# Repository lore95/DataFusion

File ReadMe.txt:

Project: ML Video Recognition & Pressure Boards for Post-Surgery Knee Rehabilitation @ KTH

INTRODUCTION
This project integrates machine learning-based video recognition and pressure boards to combine extrapolated data, generating an accurate 3D model of forces and human body movement. The main goal is to evaluate a patient's muscular power and movement fluidity, essential for monitoring progress in post-surgery knee rehabilitation.

PROBLEM STATEMENT
Evaluating muscle power and movement fluidity is crucial for tracking post-surgery recovery in patients with knee injuries. Traditionally, physiotherapists rely on qualitative assessments or expensive equipment to obtain reliable data. This project aims to provide a cost-effective, accurate, and universal solution for precise measurements through force sensors and skeleton tracking technology.

SOLUTION
Our system leverages data from four force sensors on a Wii board combined with video-based skeleton tracking to offer enhanced evaluations of knee recovery. By providing precise metrics, it complements and improves traditional methods of physiotherapy, offering a more data-driven approach to post-surgery rehabilitation.

HOW IT WORKS
Force Sensors: Four force sensors from a Wii board collect data on pressure distribution during movement.
Skeleton Tracking: Video-based skeleton tracking technology captures the movement and alignment of the patient's body.
Data Integration: Both sources of data are combined to create a 3D model that visualizes forces and motion, allowing for detailed analysis of knee recovery progress.

CONTRIBUTING
We welcome contributions! Please feel free to submit a pull request or raise an issue to discuss improvements or report bugs.

PROJECT STRUCTURE
Src/DataFusionExe
-DataFusion.py
	This file contains the code responsible for merging the data from the two core technologies used in this project: force sensors from the Wii board and video-based skeleton tracking. The integration of these datasets allows for the creation of a detailed and accurate 3D model, which is essential for evaluating a patient's post-surgery knee recovery.

-ImageRecognition AND PressureReadings:
	The folder ImageRecognition contains all the code related to skeleton tracking development and testing.
	The folder PressureReadings contains the implementation for reading force data from the Wii board's sensors.

-Requirements.txt
	The requirements.txt file lists all necessary dependencies for the project.

-yolov8m-pose.pt
	We use the yolov8m-pose.pt model for skeleton tracking.

INSTALLATION (WIP)
Clone the repository: git clone https://github.com/lore95/DataFusion.git
Install dependencies: pip install -r requirements.txt
Follow the steps in the Readme file located in PressureReadings
Run the application: python DataFusion.py

USAGE
Connect the Wii board to your USB port.
Start collecting data for post-surgery knee rehabilitation analysis.

The project communication channel: https://app.clickup.com/9012214187/v/b/s/90121097948

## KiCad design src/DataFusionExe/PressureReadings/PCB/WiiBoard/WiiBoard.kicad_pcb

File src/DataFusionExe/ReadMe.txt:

DATA INTEGRATION: FORCE SENSORS AND SKELETON TRACKING
This section contains the code responsible for merging the data from the two core technologies used in this project: force sensors from the Wii board and video-based skeleton tracking. The integration of these datasets allows for the creation of a detailed and accurate 3D model, which is essential for evaluating a patient's post-surgery knee recovery.

- The folder ImageRecognition contains all the code related to skeleton tracking development.
- The folder PressureReadings contains the implementation for reading force data from the Wii board's sensors.
- The script DataFusion.py integrates the data from both sources and runs the program.
- The requirements.txt file lists all necessary dependencies for the project.
- We use the yolov8m-pose.pt model for skeleton tracking.

INSTALLATION (WIP)
Clone the repository: git clone https://github.com/lore95/DataFusion.git
Install dependencies: pip install -r requirements.txt
Run the application: python DataFusion.py

USAGE
Connect the Wii board to your USB port.
Launch the video recognition system.
Start collecting data for post-surgery knee rehabilitation analysis.

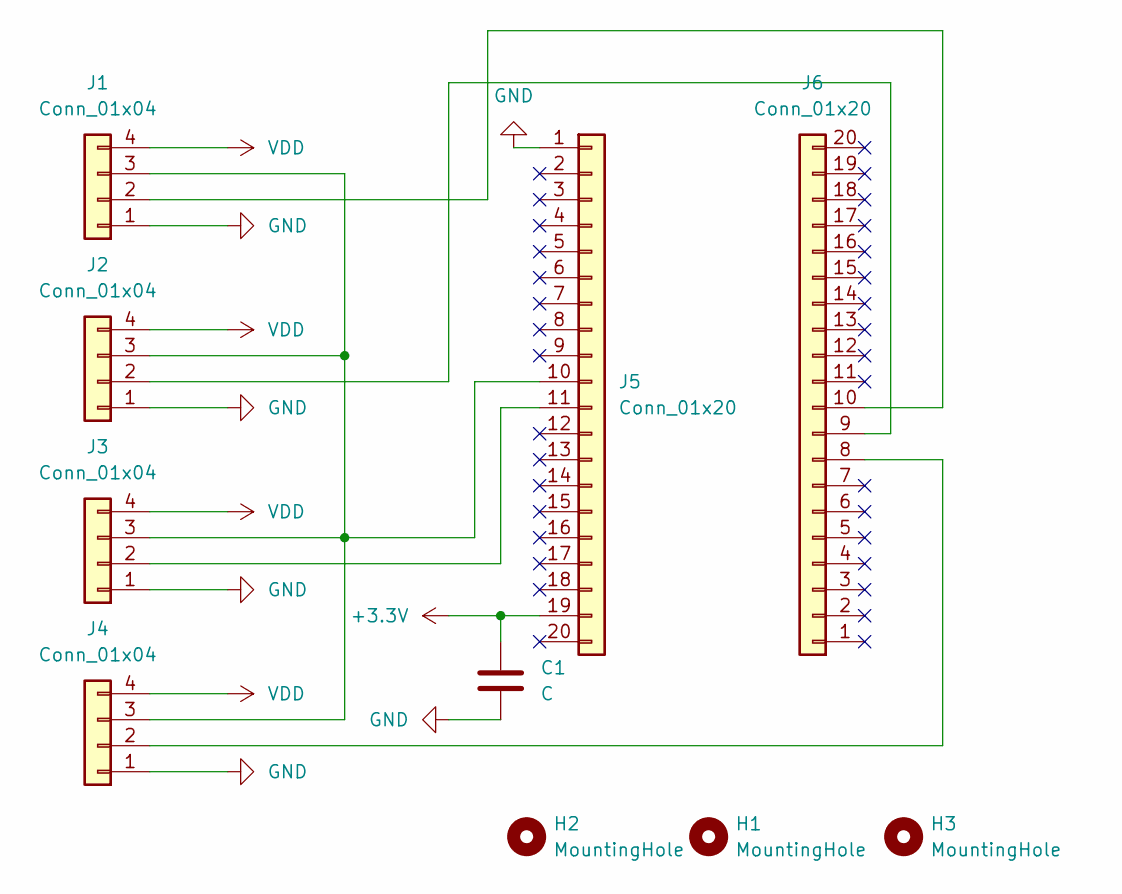
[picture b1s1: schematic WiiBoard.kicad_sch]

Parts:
C1: C; CP_Radial_D8.0mm_P5.00mm
H1, H2, H3: MountingHole; MountingHole_3.2mm_M3
J1, J2, J3, J4: Conn_01x04; PinSocket_1x04_P2.54mm_Vertical
J5, J6: Conn_01x20; PinSocket_1x20_P2.54mm_Vertical

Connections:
+3.3V: C1.1, J5.19
GND: C1.2, J1.1, J2.1, J3.1, J4.1, J5.1
unnamed: J1.2, J6.10
unnamed: J1.3, J2.3, J3.3, J4.3, J5.10
unnamed: J2.2, J6.9
unnamed: J3.2, J5.11
unnamed: J4.2, J6.8
VDD: J1.4, J2.4, J3.4, J4.4

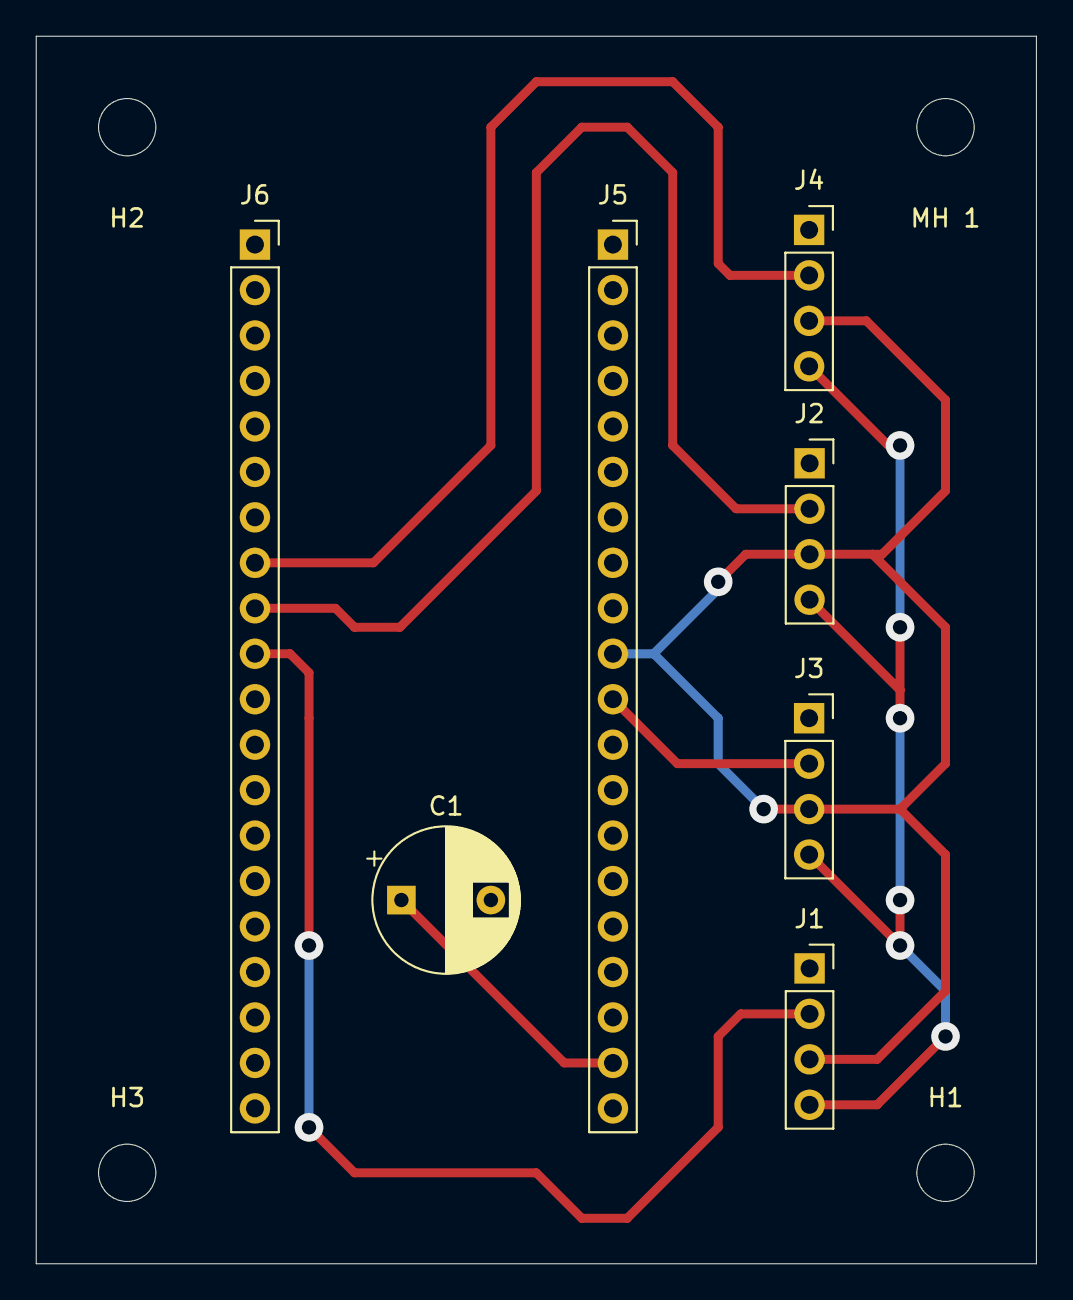
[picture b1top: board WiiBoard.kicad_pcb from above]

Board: 2 copper layers, 55.9 x 68.6 mm, 11 parts (0 on the bottom side), 8 nets.

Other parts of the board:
MH 1: MountingHole; MountingHole_3.2mm_M3

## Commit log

2024-08-29 GitHub Project Setup
2024-08-29 Update ReadMe.txt
    Just trying out
2024-08-29 Update ReadMe.txt
    Removed trash
2024-08-29 Changed clickuplink to go to board
2024-08-31 Added some files
2024-08-31 set up of structured folders for coding
2024-09-02 moves the lean canvas pdf to documentation folder
2024-09-02 Created instruction folder for openpose compilation on mac
2024-09-02 created a git ignore
2024-09-02 fixed gitignore
2024-09-19 Add files via upload
    Moved pdf to documentation folder
2024-09-19 Added ligament reconstruction pdf
2024-09-19 Renameve canvas and moved other pdf
2024-09-19 Fixed name for another pdf
2024-09-19 Ignore playground
2024-09-19 Fixed name of documentation folder
2024-09-23 wiiboard upload
2024-09-25 new wiiboard folder
2024-09-25 calibration data process
2024-09-27 experiment trials
    first equation good
2024-09-27 Experiment
    V1, V3 and V4 readings with gain 128
2024-09-27 for gain 1 and sps 40
2024-09-30 measurements with 640 SPS and 128 gain
2024-09-30 update sensitivity script
2024-09-30 V3_640_128 readings and png
2024-09-30 PLOT reg
2024-10-03 cleaning the folder pressur reading and creating a readme
2024-10-08 Fixed pathing and folder names, added skeleton tracking
2024-10-08 update location
2024-10-08 Canhged Pressure Readings folder path
2024-10-08 trial
2024-10-08 changed dir name for pressure
2024-10-11 ReadMe Updates
    Improvements on Readme's for next week's review
2024-10-11 PCB Board
    PCB First design, not fully done but great advance
2024-10-17 Fixed names
2024-10-17 Added info on readme
2024-10-17 Added info on the readme file
2024-10-17 big update
2024-10-17 PCB Corrections
2024-10-17 working update to do clean up
    very big update
2024-10-17 added filtered force value
2024-10-17 working real time code to clean up
    very very big update
2024-10-18 wiiboard
2024-10-18 Mac toolchain compilation
    Created a folder for macbook compliation
2024-10-19 Working version for both MAC and WIn
2024-10-22 Commits for mac
2024-10-22 fixed requirements
2024-10-29 update data_read
